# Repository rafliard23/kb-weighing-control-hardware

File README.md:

# Hardware PCB for Automatic Weighing Control System (ATMega328p based)
Hardware component of Automatic Weighing Control system project

© 2022 Muhammad Rafli Ardiansyah

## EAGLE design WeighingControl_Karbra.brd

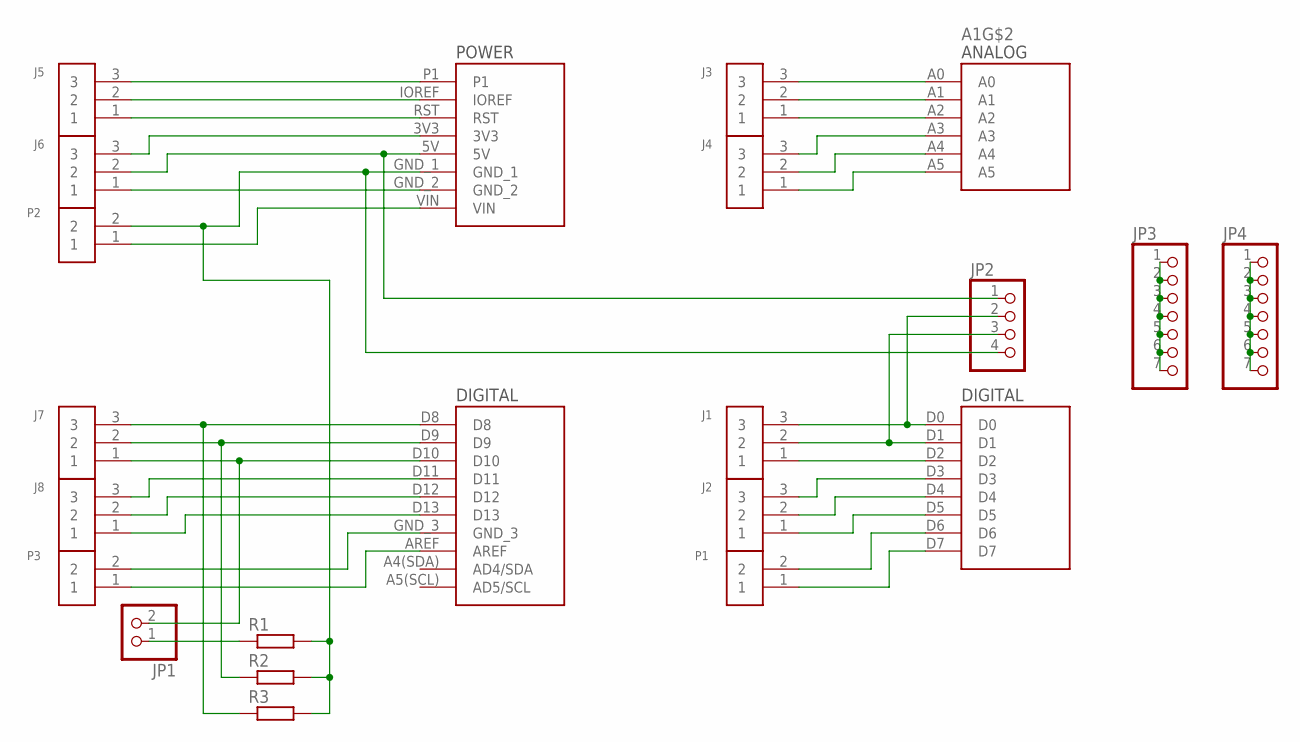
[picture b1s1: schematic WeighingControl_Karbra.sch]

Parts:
A1: A000066; ARDUINO_A000066
J1, J2, J3, J4, J5, J6, J7, J8: 282837-3; TE_282837-3
JP1: PINHD-1X2; 1X02
JP2: PINHD-1X4; 1X04
JP3, JP4: PINHD-1X7; 1X07
P1, P2, P3: 282837-2; TE_282837-2
R1, R2, R3: R-EU_0204/7; 0204/7

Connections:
unnamed: A1.A0, J3.3
unnamed: A1.A1, J3.2
unnamed: A1.A2, J3.1
unnamed: A1.A3, J4.3
unnamed: A1.A4, J4.2
unnamed: A1.A5, J4.1
unnamed: A1.D0, J1.3, JP2.2
unnamed: A1.D1, J1.2, JP2.3
unnamed: A1.D2, J1.1
unnamed: A1.D3, J2.3
unnamed: A1.D4, J2.2
unnamed: A1.D5, J2.1
unnamed: A1.D6, P1.2
unnamed: A1.D7, P1.1
unnamed: A1.P1, J5.3
unnamed: A1.IOREF, J5.2
unnamed: A1.RST, J5.1
unnamed: A1.3V3, J6.3
unnamed: A1.5V, J6.2, JP2.1
unnamed: A1.GND_1, JP2.4, P2.2, R1.2, R2.2, R3.2
unnamed: A1.GND_2, J6.1
unnamed: A1.VIN, P2.1
unnamed: A1.D8, J7.3, R3.1
unnamed: A1.D9, J7.2, R2.1
unnamed: JP1.1, R1.1
unnamed: A1.D11, J8.3
unnamed: A1.D12, J8.2
unnamed: A1.D13, J8.1
unnamed: A1.GND_3, P3.2
unnamed: A1.AREF, P3.1
unnamed: JP3.1, JP3.2, JP3.3, JP3.4, JP3.5, JP3.6, JP3.7
unnamed: JP4.1, JP4.2, JP4.3, JP4.4, JP4.5, JP4.6, JP4.7
unnamed: A1.D10, J7.1, JP1.2

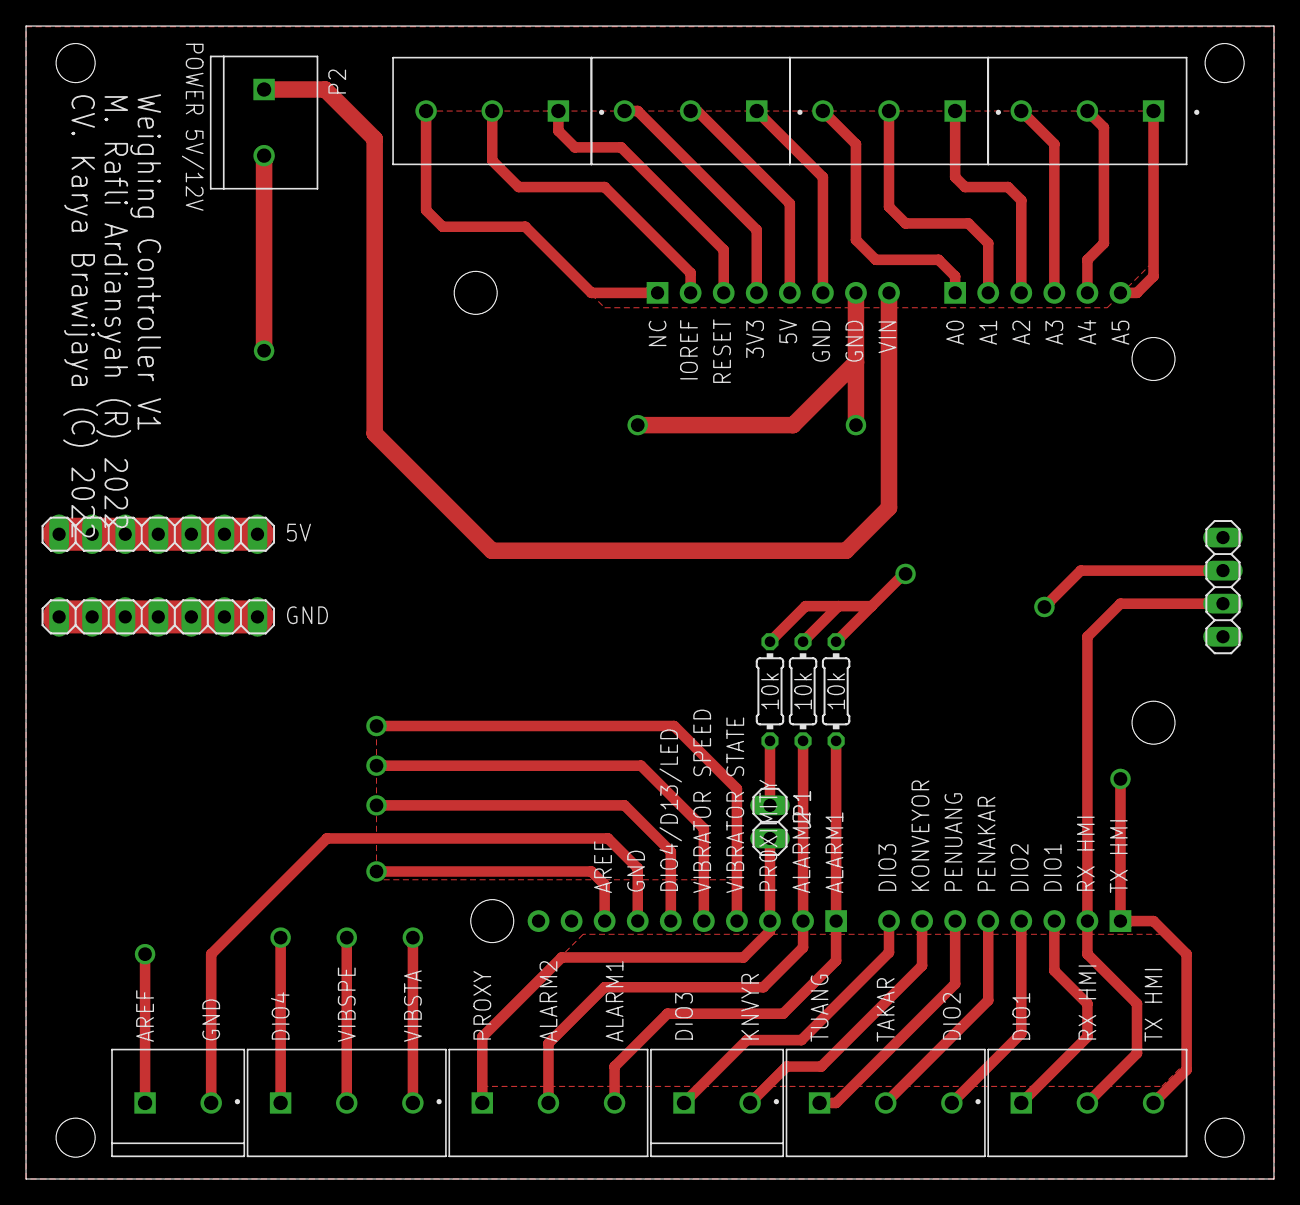
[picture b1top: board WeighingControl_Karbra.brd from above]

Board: 2 copper layers, 95.9 x 88.6 mm, 19 parts (1 on the bottom side), 33 nets.

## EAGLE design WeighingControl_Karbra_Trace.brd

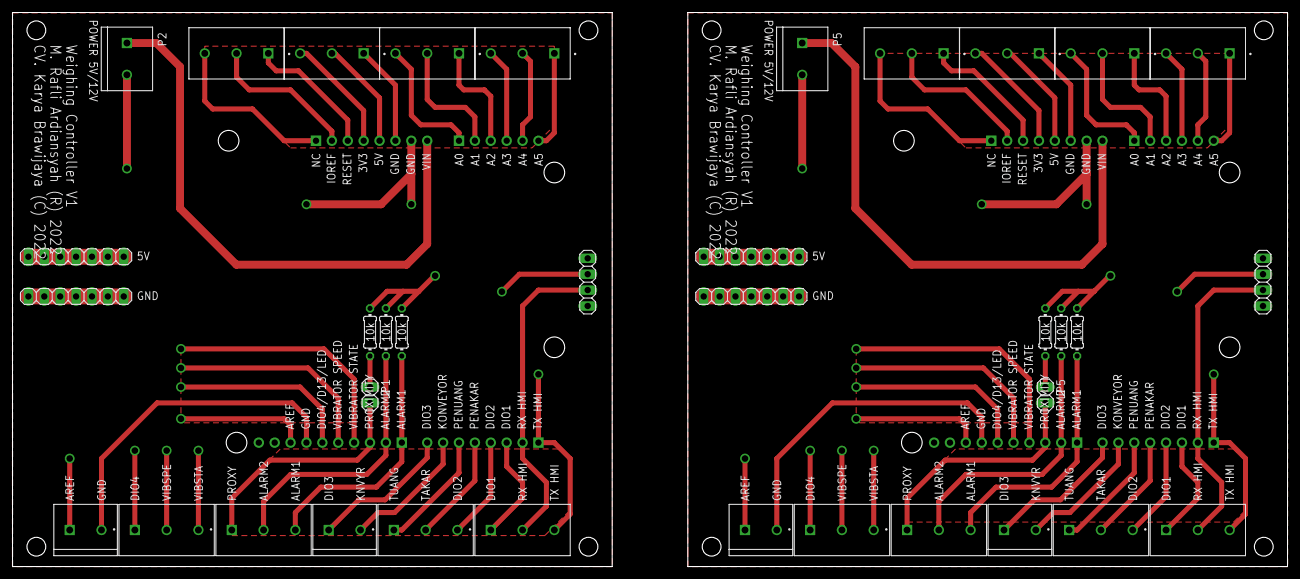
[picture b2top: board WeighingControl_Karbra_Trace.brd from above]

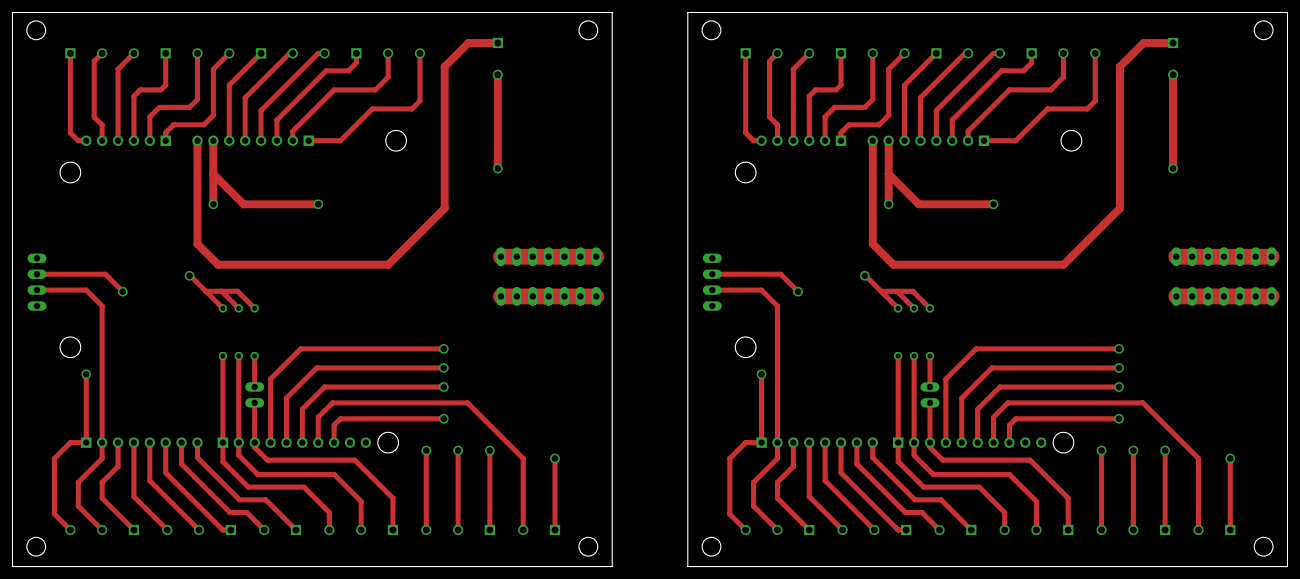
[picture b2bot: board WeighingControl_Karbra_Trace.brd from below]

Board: 2 copper layers, 203.8 x 88.6 mm, 38 parts (2 on the bottom side), 66 nets.

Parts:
A1, A2: A000066; ARDUINO_A000066
J1, J2, J3, J4, J5, J6, J7, J8, J9, J10, J11, J12, J13, J14, J15, J16: 282837-3; TE_282837-3
JP1, JP5: 1X02
JP2, JP6: 1X04
JP3, JP4, JP7, JP8: 1X07
P1, P2, P3, P4, P5, P6: 282837-2; TE_282837-2
R1, R2, R3, R4, R5, R6: 0204/7

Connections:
unnamed: A1.A0, J3.3
unnamed: A1.A1, J3.2
unnamed: A1.A2, J3.1
unnamed: A1.A3, J4.3
unnamed: A1.A4, J4.2
unnamed: A1.A5, J4.1
unnamed: A1.D0, J1.3, JP2.2
unnamed: A1.D1, J1.2, JP2.3
unnamed: A1.D2, J1.1
unnamed: A1.D3, J2.3
unnamed: A1.D4, J2.2
unnamed: A1.D5, J2.1
unnamed: A1.D6, P1.2
unnamed: A1.D7, P1.1
unnamed: A1.P1, J5.3
unnamed: A1.IOREF, J5.2
unnamed: A1.RST, J5.1
unnamed: A1.3V3, J6.3
unnamed: A1.5V, J6.2, JP2.1
unnamed: A1.GND_1, JP2.4, P2.2, R1.2, R2.2, R3.2
unnamed: A1.GND_2, J6.1
unnamed: A1.VIN, P2.1
unnamed: A1.D8, J7.3, R3.1
unnamed: A1.D9, J7.2, R2.1
unnamed: JP1.1, R1.1
unnamed: A1.D11, J8.3
unnamed: A1.D12, J8.2
unnamed: A1.D13, J8.1
unnamed: A1.GND_3, P3.2
unnamed: A1.AREF, P3.1
unnamed: JP3.1, JP3.2, JP3.3, JP3.4, JP3.5, JP3.6, JP3.7
unnamed: JP4.1, JP4.2, JP4.3, JP4.4, JP4.5, JP4.6, JP4.7
unnamed: A2.A0, J11.3
unnamed: A1.D10, J7.1, JP1.2
unnamed: A2.A1, J11.2
unnamed: A2.A2, J11.1
unnamed: A2.A3, J12.3
unnamed: A2.A4, J12.2
unnamed: A2.A5, J12.1
unnamed: A2.D0, J9.3, JP6.2
unnamed: A2.D1, J9.2, JP6.3
unnamed: A2.D2, J9.1
unnamed: A2.D3, J10.3
unnamed: A2.D4, J10.2
unnamed: A2.D5, J10.1
unnamed: A2.D6, P4.2
unnamed: A2.D7, P4.1
unnamed: A2.P1, J13.3
unnamed: A2.IOREF, J13.2
unnamed: A2.RST, J13.1
unnamed: A2.3V3, J14.3
unnamed: A2.5V, J14.2, JP6.1
unnamed: A2.VIN, P5.1
unnamed: A2.D8, J15.3, R6.1
unnamed: A2.D9, J15.2, R5.1
unnamed: A2.D11, J16.3
unnamed: A2.D12, J16.2
unnamed: A2.D13, J16.1
unnamed: A2.GND_3, P6.2
unnamed: A2.AREF, P6.1
unnamed: A2.GND_1, JP6.4, P5.2, R4.2, R5.2, R6.2
unnamed: A2.GND_2, J14.1
unnamed: A2.D10, J15.1, JP5.2
unnamed: JP5.1, R4.1
unnamed: JP7.1, JP7.2, JP7.3, JP7.4, JP7.5, JP7.6, JP7.7
unnamed: JP8.1, JP8.2, JP8.3, JP8.4, JP8.5, JP8.6, JP8.7

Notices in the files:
WeighingControl_Karbra.brd:
CV. Karya Brawijaya (C) 2022
